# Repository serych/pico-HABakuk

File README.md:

# Picoballoon tracker board based on RP2040
In this project I am developing a lightweight small balloon tracker board based on the RP2040 processor. 
The primary software intended for this board is [pico-WSPRer](https://github.com/EngineerGuy314/pico-WSPRer). 
## Basic parameters
- Board contains: 
    - RP2040 processor (with memory and crystal and RGB LED for status indication), 
    - position for soldering GPS module type ATGM336H (or pin compatible), 
    - SPV1040T MPPT inverter for solar cells 
- Flight interfaces: 
    - antenna, 
    - solar panels, 
    - ultracapacitor (optional), 
    - GPS antenna
    - additional GPIO pins GPIO10-GPIO13 + ADC0
- The pre-flight electronics parts are located on the breakaway part of the board, which is also equipped with test pins so that the flight part can be connected even after breakaway. 
- Pre-flight interfaces: 
    - USB connector and stabilizer for powering the board via USB, 
    - debug interface of RP2040, 
    - RESET and USB_BOOT buttons
## Images

### This project is licensed under the terms of the CERN Open Hardware Licence Version 2 - Weakly Reciprocal.

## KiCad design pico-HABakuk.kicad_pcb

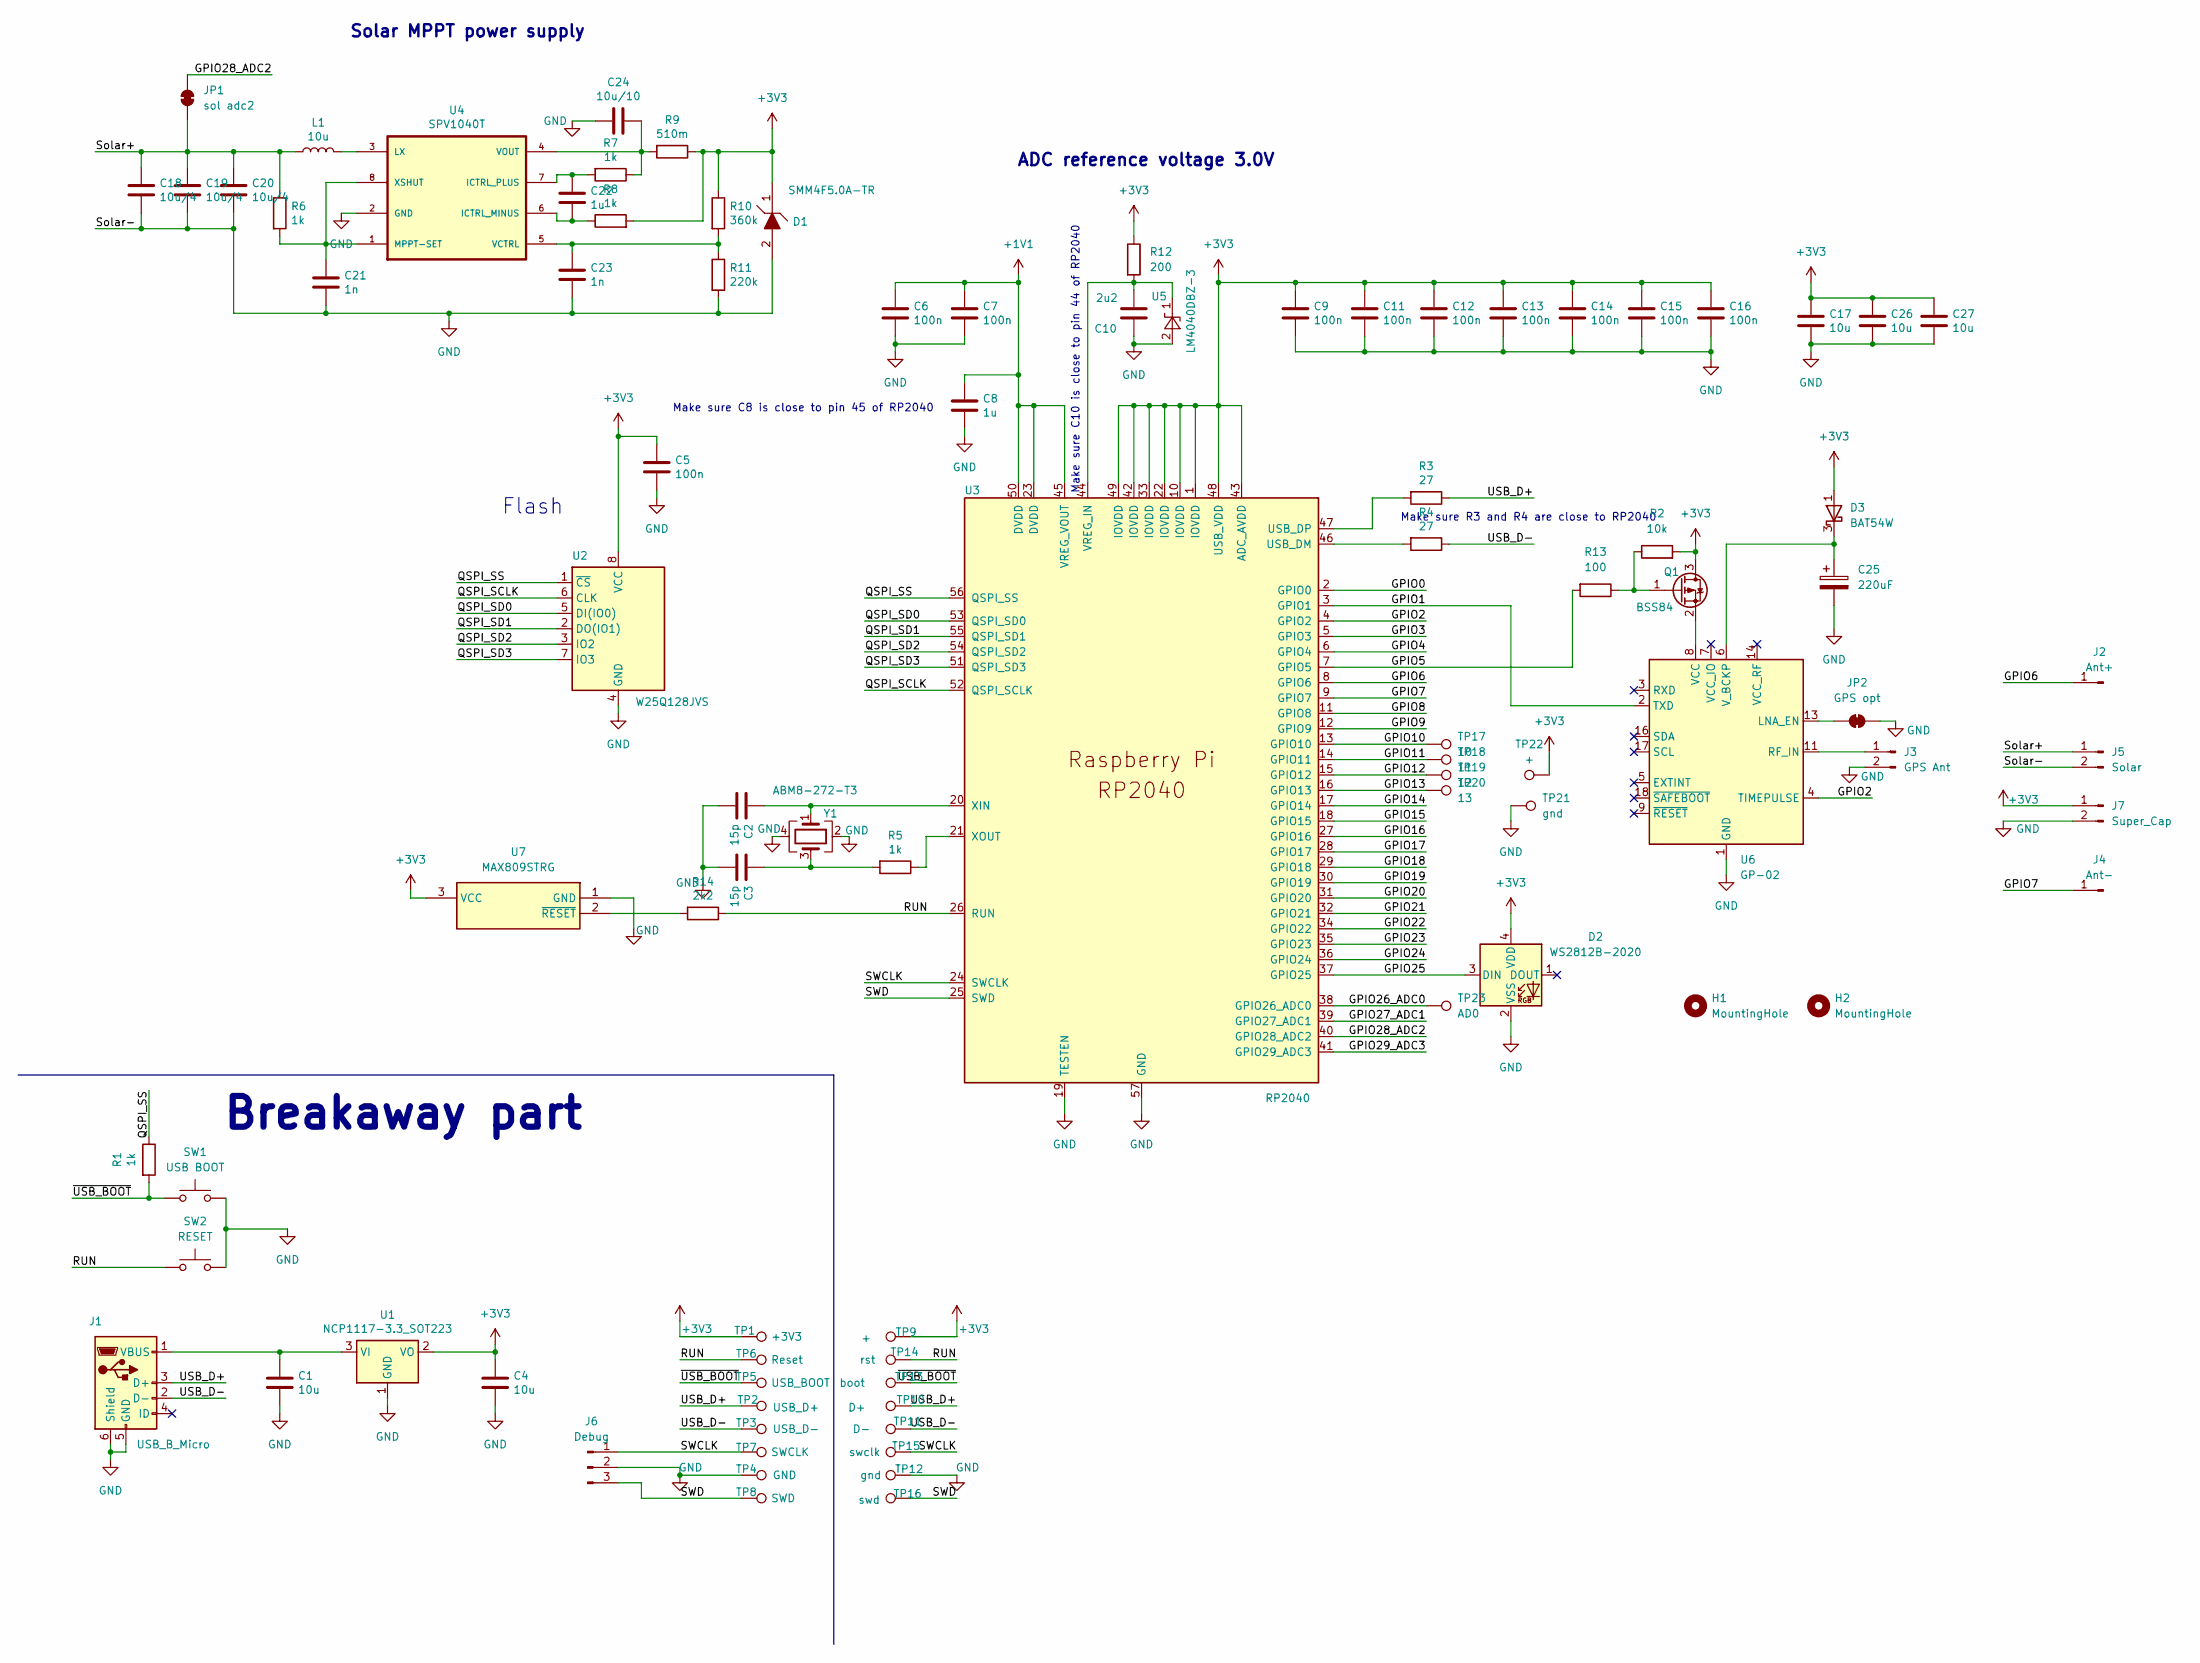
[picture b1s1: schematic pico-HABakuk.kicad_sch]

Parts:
C1, C4, C17, C26, C27: 10u; C_0805_2012Metric
C2, C3: 15p; C_0603_1608Metric
C5, C6, C7, C9, C11, C12, C13, C14, C15, C16: 100n; C_0603_1608Metric
C8, C22: 1u; C_0603_1608Metric
C10: 2u2; C_0603_1608Metric
C18, C19, C20: 10u/4; C_0603_1608Metric
C21, C23: 1n; C_0603_1608Metric
C24: 10u/10; C_0805_2012Metric
C25: 220uF; CP_EIA-3216-10_Kemet-I
D1: SMM4F5.0A-TR; SMM4F15ATR; Mouser Part Number 511-SMM4F5.0A-TR
D2: WS2812B-2020; LED_WS2812B-2020_PLCC4_2.0x2.0mm
D3: BAT54W; SOT-323_SC-70
H1, H2: MountingHole; MountingHole_2.1mm
J1: USB_B_Micro; USB_Micro-B_Amphenol_10103594-0001LF_Horizontal_modified
J2: Ant+; PinHeader_1x01_P2.54mm_Vertical
J3: GPS Ant; PinSocket_1x02_P2.54mm_Vertical
J4: Ant-; PinHeader_1x01_P2.54mm_Vertical
J5: Solar; PinSocket_1x02_P2.54mm_Vertical
J6: Debug; PinHeader_1x03_P2.54mm_Vertical
J7: Super_Cap; PinSocket_1x02_P2.54mm_Vertical
JP1: sol adc2; SolderJumper-2_P1.3mm_Bridged_RoundedPad1.0x1.5mm
JP2: GPS opt; SolderJumper-2_P1.3mm_Bridged_RoundedPad1.0x1.5mm
L1: 10u; L_Taiyo-Yuden_MD-3030
Q1: BSS84; SOT-23
R1, R5, R6, R7, R8: 1k; R_0603_1608Metric
R2: 10k; R_0603_1608Metric
R3, R4: 27; R_0603_1608Metric
R9: 510m; R_0603_1608Metric
R10: 360k; R_0603_1608Metric
R11: 220k; R_0603_1608Metric
R12: 200; R_0603_1608Metric
R13: 100; R_0603_1608Metric
R14: 2k2; R_0603_1608Metric
SW1: USB BOOT; SW_SPST_Omron_B3FS-100xP
SW2: RESET; SW_SPST_Omron_B3FS-100xP
TP1: +3V3; Pin_D1.1mm_L10.2mm_W3.5mm_Flat
TP2: USB_D+; Pin_D1.1mm_L10.2mm_W3.5mm_Flat
TP3: USB_D-; Pin_D1.1mm_L10.2mm_W3.5mm_Flat
TP4: GND; Pin_D1.1mm_L10.2mm_W3.5mm_Flat
TP5: USB_BOOT; Pin_D1.1mm_L10.2mm_W3.5mm_Flat
TP6: Reset; Pin_D1.1mm_L10.2mm_W3.5mm_Flat
TP7: SWCLK; Pin_D1.1mm_L10.2mm_W3.5mm_Flat
TP8: SWD; Pin_D1.1mm_L10.2mm_W3.5mm_Flat
TP9: +; TestPoint_Pad_D1.5mm
TP10: D+; TestPoint_Pad_D1.5mm
TP11: D-; TestPoint_Pad_D1.5mm
TP12: gnd; TestPoint_Pad_D1.5mm
TP13: boot; TestPoint_Pad_D1.5mm
TP14: rst; TestPoint_Pad_D1.5mm
TP15: swclk; TestPoint_Pad_D1.5mm
TP16: swd; TestPoint_Pad_D1.5mm
TP17: 10; TestPoint_THTPad_D1.0mm_Drill0.5mm
TP18: 11; TestPoint_THTPad_D1.0mm_Drill0.5mm
TP19: 12; TestPoint_THTPad_D1.0mm_Drill0.5mm
TP20: 13; TestPoint_THTPad_D1.0mm_Drill0.5mm
TP21: gnd; TestPoint_THTPad_D1.0mm_Drill0.5mm
TP22: +; TestPoint_THTPad_D1.0mm_Drill0.5mm
TP23: AD0; TestPoint_THTPad_D1.0mm_Drill0.5mm
U1: NCP1117-3.3_SOT223; SOT-223-3_TabPin2
U2: W25Q128JVS; SOIC-8_5.23x5.23mm_P1.27mm
U3: RP2040; RP2040-QFN-56
U4: SPV1040T; TSSOP-8_4.4x3mm_P0.65mm
U5: LM4040DBZ-3; SOT-23
U6: GP-02; ublox_MAX
U7: MAX809STRG; SOT65P210X110-3N; Mouser Part Number 700-MAX809SEXRT
Y1: ABM8-272-T3; Crystal_SMD_3225-4Pin_3.2x2.5mm

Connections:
+1V1: C6.1, C7.1, C8.1, U3.23 (DVDD), U3.45 (VREG_VOUT), U3.50 (DVDD)
+3V3: C4.1, C5.1, C9.1, C11.1, C12.1, C13.1, C14.1, C15.1, C16.1, C17.1, C26.1, C27.1, D1.1, D1.3, D2.4 (VDD), D3.1 (A), J7.1, Q1.3 (D), R2.2, R8.2, R9.1, R10.1, R12.1, TP1.1, TP9.1, TP22.1, U1.2 (VO), U2.8 (VCC), U3.1 (IOVDD), U3.10 (IOVDD), U3.22 (IOVDD), U3.33 (IOVDD), U3.42 (IOVDD), U3.43 (ADC_AVDD), U3.48 (USB_VDD), U3.49 (IOVDD), U7.3 (VCC)
/GPIO0: U3.2 (GPIO0)
/GPIO1: U3.3 (GPIO1), U6.2 (TXD)
/GPIO2: U3.4 (GPIO2), U6.4 (TIMEPULSE)
/GPIO3: U3.5 (GPIO3)
/GPIO4: U3.6 (GPIO4)
/GPIO5: R13.2, U3.7 (GPIO5)
/GPIO6: J2.1, U3.8 (GPIO6)
/GPIO7: J4.1, U3.9 (GPIO7)
/GPIO8: U3.11 (GPIO8)
/GPIO9: U3.12 (GPIO9)
/GPIO10: TP17.1, U3.13 (GPIO10)
/GPIO11: TP18.1, U3.14 (GPIO11)
/GPIO12: TP19.1, U3.15 (GPIO12)
/GPIO13: TP20.1, U3.16 (GPIO13)
/GPIO14: U3.17 (GPIO14)
/GPIO15: U3.18 (GPIO15)
/GPIO16: U3.27 (GPIO16)
/GPIO17: U3.28 (GPIO17)
/GPIO18: U3.29 (GPIO18)
/GPIO19: U3.30 (GPIO19)
/GPIO20: U3.31 (GPIO20)
/GPIO21: U3.32 (GPIO21)
/GPIO22: U3.34 (GPIO22)
/GPIO23: U3.35 (GPIO23)
/GPIO24: U3.36 (GPIO24)
/GPIO25: D2.3 (DIN), U3.37 (GPIO25)
/GPIO26_ADC0: TP23.1, U3.38 (GPIO26_ADC0)
/GPIO27_ADC1: U3.39 (GPIO27_ADC1)
/GPIO28_ADC2: JP1.2 (B), U3.40 (GPIO28_ADC2)
/GPIO29_ADC3: U3.41 (GPIO29_ADC3)
/QSPI_SCLK: U2.6 (CLK), U3.52 (QSPI_SCLK)
/QSPI_SD0: U2.5 (DI(IO0)), U3.53 (QSPI_SD0)
/QSPI_SD1: U2.2 (DO(IO1)), U3.55 (QSPI_SD1)
/QSPI_SD2: U2.3 (IO2), U3.54 (QSPI_SD2)
/QSPI_SD3: U2.7 (IO3), U3.51 (QSPI_SD3)
/QSPI_SS: R1.1, U2.1 (~CS), U3.56 (QSPI_SS)
/RUN: R14.1, SW2.1, TP6.1, TP14.1, U3.26 (RUN)
/SWCLK: J6.1, TP7.1, TP15.1, U3.24 (SWCLK)
/SWD: J6.3, TP8.1, TP16.1, U3.25 (SWD)
/Solar+: C18.1, C19.1, C20.1, J5.1, JP1.1 (A), L1.1, R6.1
/USB_D+: J1.3 (D+), R3.1, TP2.1, TP10.1
/USB_D-: J1.2 (D-), R4.1, TP3.1, TP11.1
/~USB_BOOT: R1.2, SW1.1, TP5.1, TP13.1
GND: C1.2, C2.2, C3.2, C4.2, C5.2, C6.2, C7.2, C8.2, C9.2, C10.2, C11.2, C12.2, C13.2, C14.2, C15.2, C16.2, C17.2, C18.2, C19.2, C20.2, C21.2, C23.2, C24.2, C25.2, C26.2, C27.2, D1.2, D2.2 (VSS), J1.5 (GND), J1.6 (Shield), J3.2, J5.2, J6.2, J7.2, JP2.1 (A), R11.2, SW1.2, SW2.2, TP4.1, TP12.1, TP21.1, U1.1 (GND), U2.4 (GND), U3.19 (TESTEN), U3.57 (GND), U4.2 (GND), U5.2 (A), U6.1 (GND), U6.10 (GND), U6.12 (GND), U7.1 (GND), Y1.2, Y1.4
unnamed: C3.1, R5.2, Y1.3
unnamed: C25.1, D3.3 (K), U6.6 (V_BCKP)
unnamed: C1.1, J1.1 (VBUS), U1.3 (VI)
unnamed: J3.1, U6.11 (RF_IN)
unnamed: JP2.2 (B), U6.13 (LNA_EN)
unnamed: Q1.1 (G), R2.1, R13.1
unnamed: Q1.2 (S), U6.8 (VCC)
unnamed: R4.2, U3.46 (USB_DM)
unnamed: R3.2, U3.47 (USB_DP)
unnamed: C10.1, R12.2, U3.44 (VREG_IN), U5.1 (K)
unnamed: C2.1, U3.20 (XIN), Y1.1
unnamed: R5.1, U3.21 (XOUT)
unnamed: C22.2, R8.1, U4.6 (ICTRL_MINUS)
unnamed: C22.1, R7.2, U4.7 (ICTRL_PLUS)
unnamed: L1.2, U4.3 (LX)
unnamed: C21.1, R6.2, U4.1 (MPPT-SET), U4.8 (XSHUT)
unnamed: C23.1, R10.2, R11.1, U4.5 (VCTRL)
unnamed: C24.1, R7.1, R9.2, U4.4 (VOUT)
unnamed: R14.2, U7.2 (~RESET)

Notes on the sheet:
ADC reference voltage 3.0V
Breakaway part
Make sure C8 is close to pin 45 of RP2040
Solar MPPT power supply
Make sure C10 is close to pin 44 of RP2040
Make sure R3 and R4 are close to RP2040
Flash

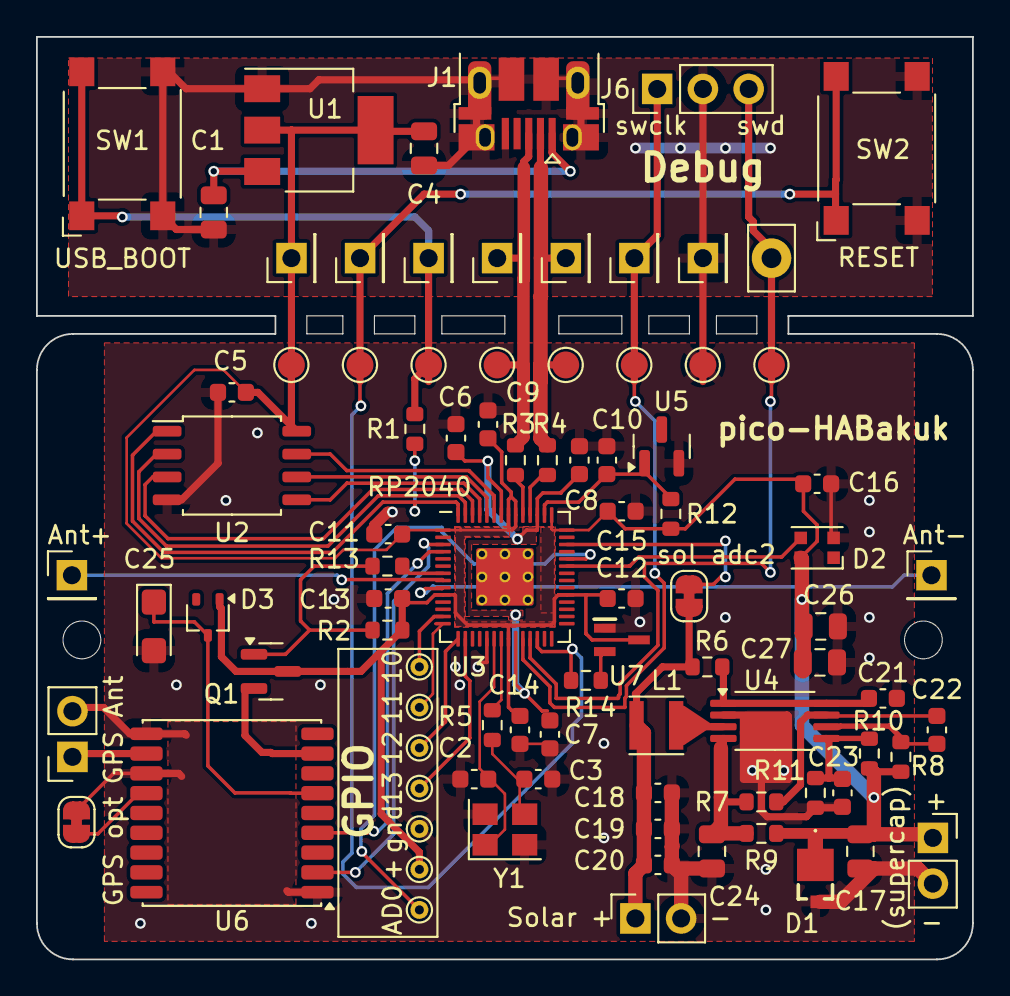
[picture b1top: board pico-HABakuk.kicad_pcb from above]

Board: 2 copper layers, 52.0 x 51.2 mm, 90 parts (0 on the bottom side), 47 nets.

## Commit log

2024-06-15 Initial commit with RP2040 minimal board KiCAD project
2024-06-15 CERN Open Hardware License added
2024-06-15 First changes in the sch and pcb
2024-06-16 Solar MPPT regulator copied into schema
2024-06-16 adding parts to schematics
2024-06-24 More work on schematics
2024-06-26 GPS module added to schematics
2024-06-26 GPS 3D model added
2024-06-26 another GPS module 3D model
2024-06-26 More work on schematics and PCB
2024-07-06 Max809 added
2024-07-10 Work on PCB
2024-07-17 board finetuning, GPIO pins added
2024-07-17 README edit
2024-07-17 README minor changes
2024-07-20 Final board tuning and DRC debuging
2024-07-20 HTML BOM added
2024-07-20 Minor silkscreen edits
2024-07-20 Gerber files generated
2024-07-20 Gerber ziped
2024-07-20 New actual images
